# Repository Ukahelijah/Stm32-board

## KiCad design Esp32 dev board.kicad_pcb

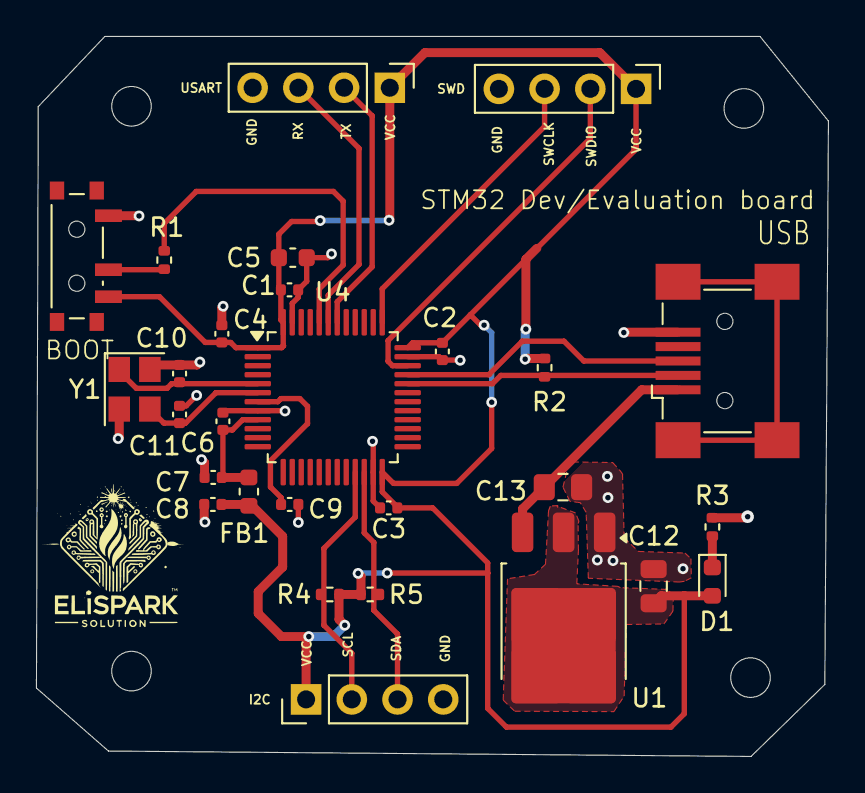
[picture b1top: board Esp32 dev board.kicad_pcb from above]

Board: 2 copper layers, 44.0 x 40.0 mm, 32 parts (0 on the bottom side), 18 nets.

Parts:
C1, C2, C3, C4, C9: 100n; C_0402_1005Metric
C5: 10u; C_0603_1608Metric
C6: 10n; C_0402_1005Metric
C7, C8: 1u; C_0402_1005Metric
C10, C11: 10p; C_0402_1005Metric
C12: 22u; C_0805_2012Metric
C13: 22u; C_0805_2012Metric_Pad1.18x1.45mm_HandSolder
D1: RED; LED_0603_1608Metric
FB1: 120R; L_0603_1608Metric
H1, H2, H3, H4: MountingHole_2.2mm_M2
J1: USB_B_Micro; USB_Mini-B_Wuerth_65100516121_Horizontal
J2, J3, J4: Conn_01x04_Pin; PinHeader_1x04_P2.54mm_Vertical
R1: 10k; R_0402_1005Metric
R2, R3, R4, R5: 1k5; R_0402_1005Metric
SW1: SW_SPDT; SW_SPDT_PCM12
U1: AMS1117CD-3.3; TO-252-3_TabPin2
U4: STM32F103C8T6; LQFP-48_7x7mm_P0.5mm
Y1: 16MHZ; Crystal_SMD_3225-4Pin_3.2x2.5mm

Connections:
+3.3V: C1.1, C2.1, C3.1, C4.1, C5.1, C8.1, C12.1, D1.2 (A), FB1.2, J2.1, J3.1, J4.1, R2.1, R4.1, R5.1, SW1.3 (C), U1.2 (VO), U4.1 (VBAT), U4.24 (VDD), U4.36 (VDD), U4.48 (VDD)
+3.3VA: C6.1, C7.1, FB1.1, U4.9 (VDDA)
/BOOT0: R1.1, SW1.2 (B)
/HSE_IN: C10.1, U4.5 (PD0), Y1.1
/HSE_OUT: C11.1, U4.6 (PD1), Y1.3
/I2C2_SCL: J4.2, R4.2, U4.21 (PB10)
/I2C2_SDA: J4.3, R5.2, U4.22 (PB11)
/NRST: C9.1, U4.7 (NRST)
/SWCLK: J2.3, U4.37 (PA14)
/SWDIO: J2.2, U4.34 (PA13)
/USART_RX: J3.3, U4.43 (PB7)
/USART_TX: J3.2, U4.42 (PB6)
/USB_D+: J1.3 (D+), U4.33 (PA12)
/USB_D-: J1.2 (D-), R2.2, U4.32 (PA11)
/pwr_led_k: D1.1 (K), R3.1
GND: C1.2, C2.2, C3.2, C4.2, C5.2, C6.2, C7.2, C8.2, C9.2, C10.2, C11.2, C12.2, C13.2, J1.5 (GND), J2.4, J3.4, J4.4, R3.2, SW1.1 (A), U1.1 (GND), U4.8 (VSSA), U4.23 (VSS), U4.35 (VSS), U4.47 (VSS), Y1.2, Y1.4
unnamed: R1.2, U4.44 (BOOT0)
VBUS: C13.1, J1.1 (VBUS), U1.3 (VI)
